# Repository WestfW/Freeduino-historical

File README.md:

Freeduino-historical:
Files and history of the ~2007 "Freeduino" project.

# <div align="center">The Freeduino Story</div>
### <div align="center">by Bill Westfield (WestfW)</div>
---

Back in about 2007, Arduino was small but rapidly growing.
Diecilmilla had been released, but the publication of its CAD files
was behind, and there was noise that perhaps the "open source
hardware" days of Arduino were behind them.  Supplies of real Arduinos
were a bit short, and there were a couple of users who were upset that
they could not manufacture their own "in bulk" for classroom
situations, and several vendors that were upset that they were unable
to negotiate the ability to sell genuine Arduinos with Arduino
themselves (or at least, not at terms that they liked.  (But I think
mostly just due to supply constraints.))

Anyway, "we" wound up with one particularly passionate user (Daniel),
one motivated vendor (NKC Electronics), a low-level guy with some
EE and low-level background looking to improve his EAGLE skills (Me!
(WestfW)), and a couple of other contibuters (notably Solarbotics and
Scott), determined to create a "truly open-source" version of the
Arduino without any of the restrictions that the Arduino Company
seemed to be considering (not even a Trademark!)

We never met.  There was much discussion via email, and a forum that
Daniel set up.  Eventually, I had four EAGLE designs mostly similar to
the Duemilanove - one using mostly throughole components, and one each
using 0603, 0805, an 1206 SMT components.  I thought we were still
discussing things, and suddenly NKC piped up with "Well, I've ordered
100 bare PCBs of each version, and we'll see how they go"!  I was a
bit shocked; I had been putting a lot of time into the project, but
JUST time.  Ordering 400 PCBs represented "real money"!

Once a couple of boards of each type had been assembled (at/by NKC), a
decision was made to focus on the through-hole design, so that it
could be sold as a kit.  This would both appeal the the people coming
at Arduino from the Electronics Hobbyist side of the world, as well as
saving some manufacturing costs (this was well before "cheap SMT
assembly services" were common.)  Additional revisions to the design
were made with this in mind.  For example, the board was expanded
slightly to make more room, and the voltage regulator was changed to a
full-sized TO220.

---

I guess the design was a success.  NKC sold Freeduino kits for quite a
few years, Solarbotics sold their (somewhat diffrent) design, and
... various PCBs appeared from strange places, complete with the
little "PCB by WestfW" trace in the corner.  Also, Arduino
re-committed to Open-source principles, and apparently started
accepting more vendors as resellers, making the design somewhat
superfulous.  And then the cheap clones from China appeared, along
with cheaper PCB services, a more formal OSHW movement, and newer,
better, and lower-cost designs showed up from ... lots of places.  I
think Freeduino is no longer *necessary*.  But I like to think that it
was a useful "nudge" toward the way things are today.

---

See also:

https://forum.arduino.cc/t/arduino-vs-freeduino-what-is-the-difference/24209/2
https://forum.arduino.cc/t/freeduino-universe/6800/
https://forum.arduino.cc/t/diecimila-pcb-files/2116/

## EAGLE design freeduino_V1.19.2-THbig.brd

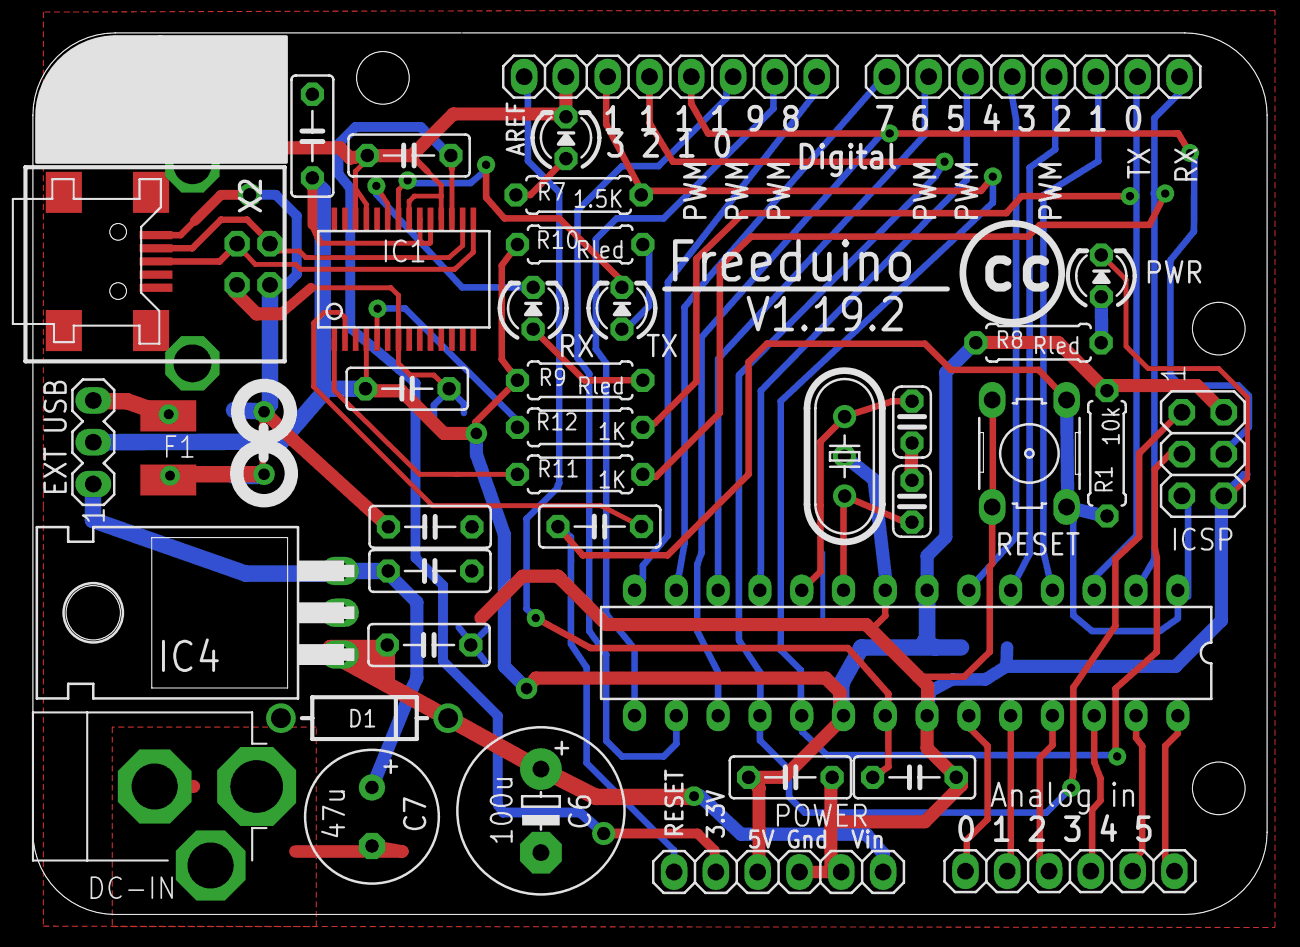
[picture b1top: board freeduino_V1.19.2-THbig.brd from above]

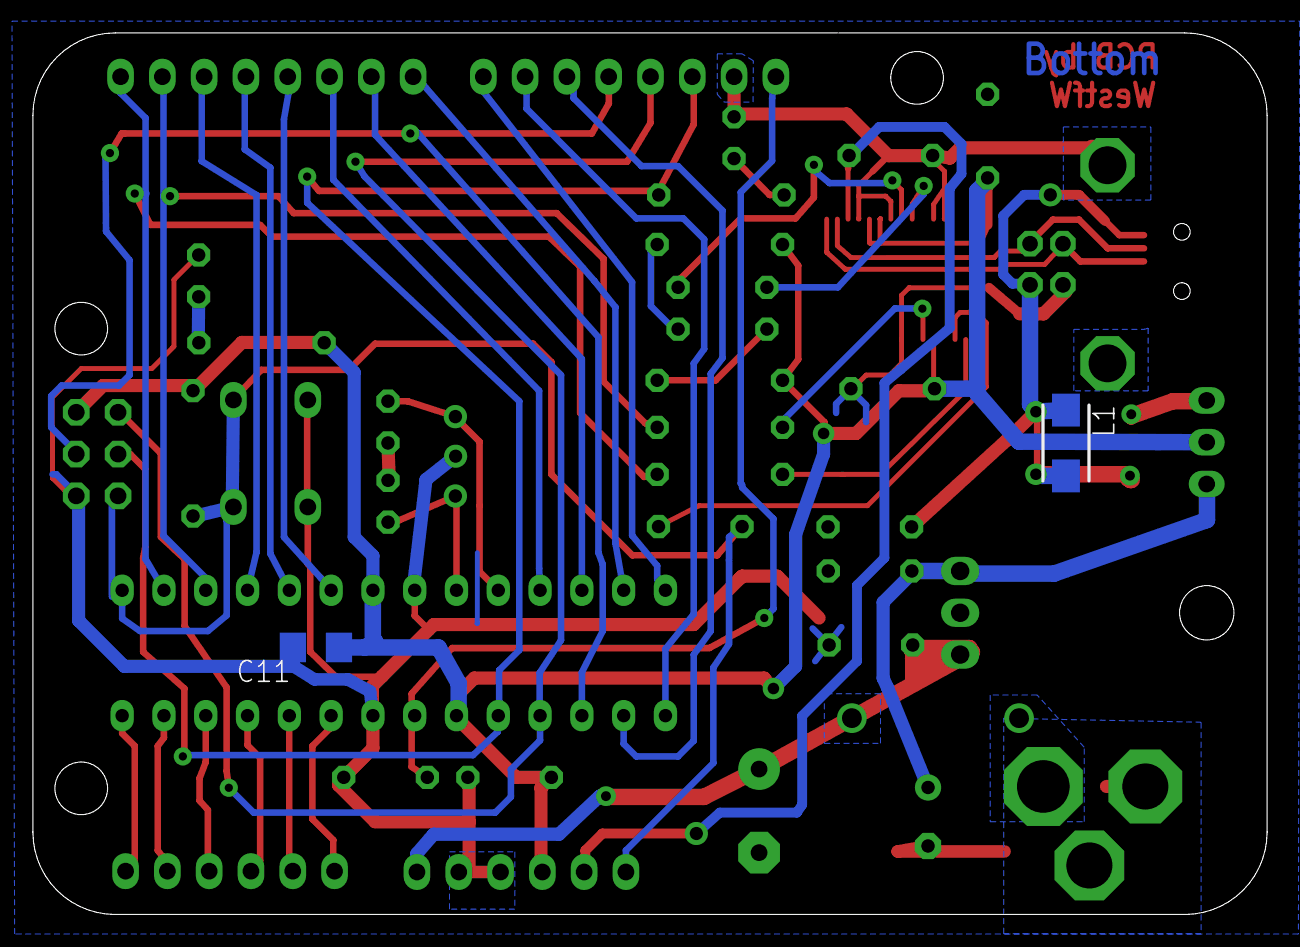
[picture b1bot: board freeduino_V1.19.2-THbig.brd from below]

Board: 2 copper layers, 75.0 x 53.6 mm, 44 parts (2 on the bottom side), 43 nets.

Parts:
BVALUE: ATMEGA168; DIL28-3
C1, C5, C8, C9, C10, C12: 100n; C050-025X075
C2, C3: 22pf; C025-024X044
C4: 10n; C050-025X075
C6: 100u; E5-10,5
C7: 47u; E3,5-8
C11: 100n; C1206
C13: 4u7; C050-025X075
CRS: 100n; C050-025X075
D1: 1N4004; DIODE-0.4
F1: PTC1812; C1812
FB1: FB3.8
IC1: FT232RL; SSOP28DB
IC4: 7805T; TO220H
ICSP: ICSP; 2X03
J1, J3: 1X08
J2: 1X06
JP1: 1X06
L1: SM-B5
P13: LED3MM
PWR: LED3MM
Q1: 16Mhz; HC49U-V
R1: 10k; 0207/7
R7: 1.5K; 0207/7
R8, R9, R10: Rled; 0207/7
R11, R12: 1K; 0207/7
RESET: B3F-10XX
RX: LED3MM
SV1: MA03-1
TX: LED3MM
U$1: DC-IN; 4UCON-POWER-JACK
U$2: MINIUSB; UX60A-MB-5SY
U$3: CC-LOGO
X2: USB-WSHIELDPADS

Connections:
+5V: BVALUE.7, BVALUE.20, C1.1, C10.2, C11.2, C13.2, IC1.4, IC1.19, IC1.20, ICSP.2, JP1.3, R1.2, R8.1, R9.1, R10.1, SV1.2
AREF: BVALUE.21, C9.1, J1.8
GND: BVALUE.8, BVALUE.22, C1.2, C2.1, C3.1, C4.1, C5.1, C6.-, C7.-, C8.2, C9.2, C10.1, C11.1, C12.1, C13.1, IC1.7, IC1.18, IC1.21, IC1.25, IC1.26, IC4.2, ICSP.6, J1.7, JP1.4, JP1.5, P13.K, PWR.K, RESET.3, RESET.4, U$1.1, U$1.3, U$2.5, X2.4, X2.SH1, X2.SH2
M8RXD: IC1.1, R11.1
M8TXD: IC1.5, R12.1
unnamed: BVALUE.15, J1.2
unnamed: PWR.A, R8.2
unnamed: IC1.23, RX.K
unnamed: BVALUE.9, C2.2, Q1.2
unnamed: F1.2, SV1.3
unnamed: D1.A, U$1.2
unnamed: IC1.16, U$2.2, X2.2
unnamed: BVALUE.4, J3.3
unnamed: BVALUE.5, J3.4
unnamed: BVALUE.6, J3.5
unnamed: BVALUE.11, J3.6
unnamed: BVALUE.12, J3.7
unnamed: BVALUE.13, J3.8
unnamed: BVALUE.23, J2.1
unnamed: BVALUE.24, J2.2
unnamed: BVALUE.25, J2.3
unnamed: BVALUE.26, J2.4
unnamed: BVALUE.27, J2.5
unnamed: BVALUE.28, J2.6
unnamed: BVALUE.3, J3.2, R12.2
unnamed: BVALUE.16, J1.3
unnamed: IC1.15, U$2.3, X2.3
unnamed: BVALUE.18, ICSP.1, J1.5
unnamed: BVALUE.14, J1.1
unnamed: IC1.22, TX.K
unnamed: BVALUE.10, C3.2, Q1.1
unnamed: P13.A, R7.1
unnamed: R10.2, TX.A
unnamed: C4.2, F1.1, FB1.P$1, FB1.P$2, L1.1, L1.2, U$2.1, X2.1
unnamed: R9.2, RX.A
unnamed: CRS.1, IC1.2
unnamed: BVALUE.17, ICSP.4, J1.4
unnamed: BVALUE.2, J3.1, R11.2
RESET: BVALUE.1, CRS.2, ICSP.5, JP1.1, R1.1, RESET.1, RESET.2
SCK: BVALUE.19, ICSP.3, J1.6, R7.2
VCC: C7.+, C12.2, IC4.3, SV1.1
VCC3V0: C8.1, IC1.17, JP1.2
VIN: C5.2, C6.+, D1.C, IC4.1, JP1.6

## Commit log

2022-10-08 Initial checkin
